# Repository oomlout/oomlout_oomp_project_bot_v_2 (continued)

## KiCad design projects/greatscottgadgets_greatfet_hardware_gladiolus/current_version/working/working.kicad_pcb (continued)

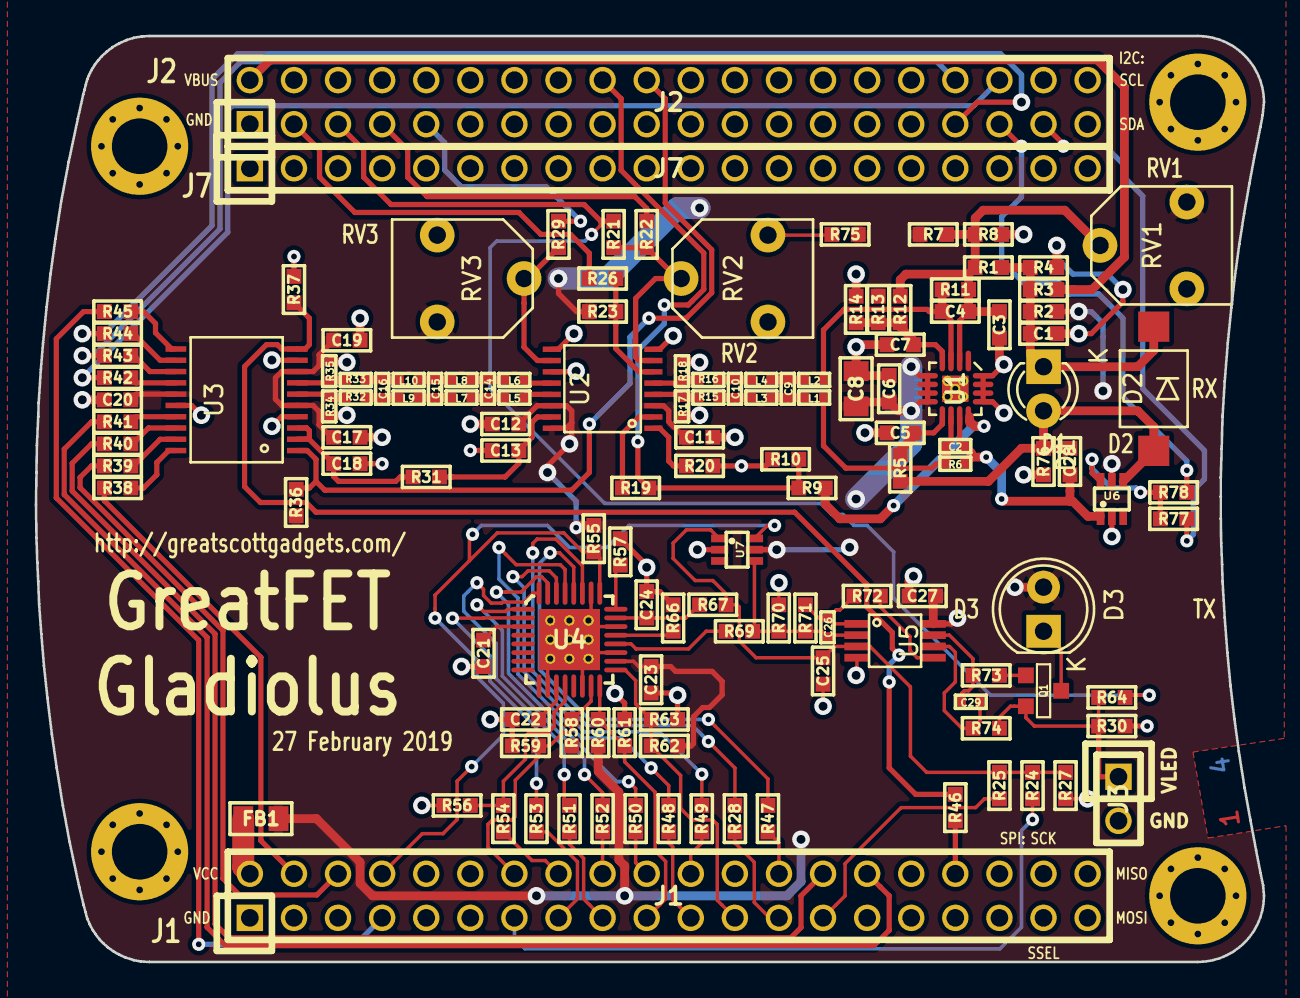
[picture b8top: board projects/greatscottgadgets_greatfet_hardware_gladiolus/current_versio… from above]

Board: 4 copper layers, 70.7 x 53.3 mm, 138 parts (0 on the bottom side), 101 nets.
